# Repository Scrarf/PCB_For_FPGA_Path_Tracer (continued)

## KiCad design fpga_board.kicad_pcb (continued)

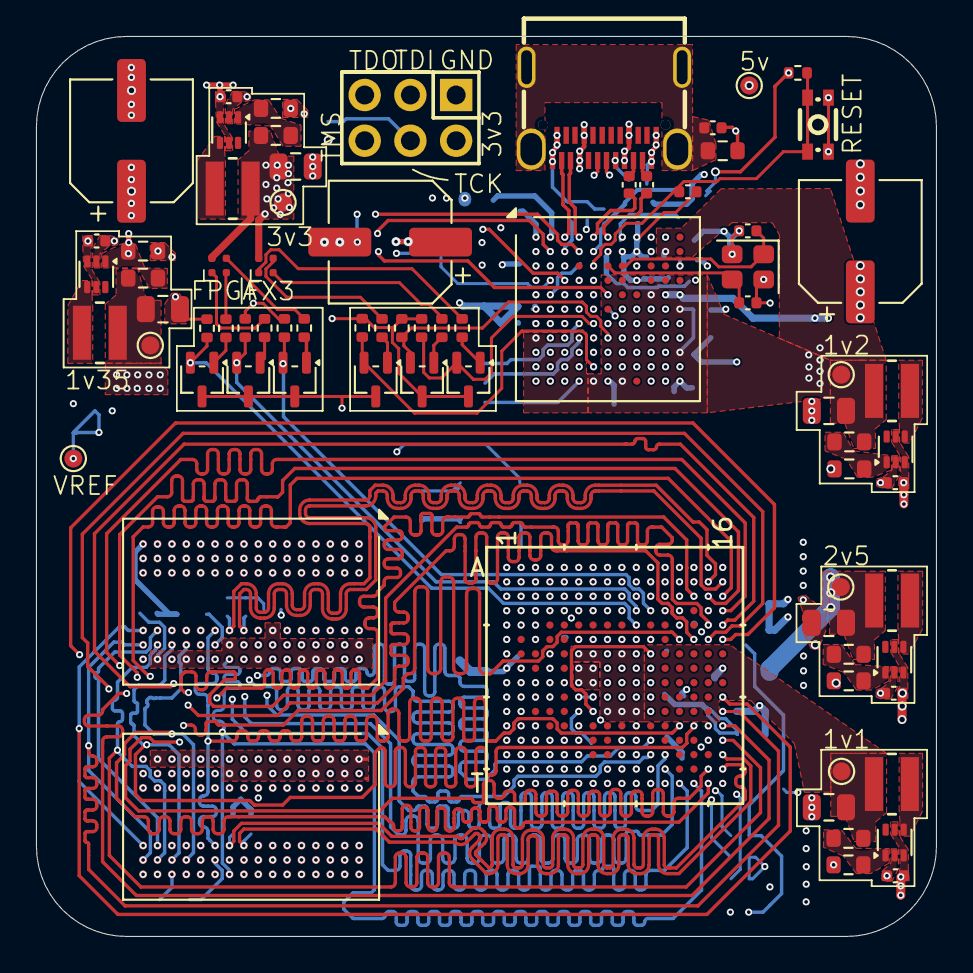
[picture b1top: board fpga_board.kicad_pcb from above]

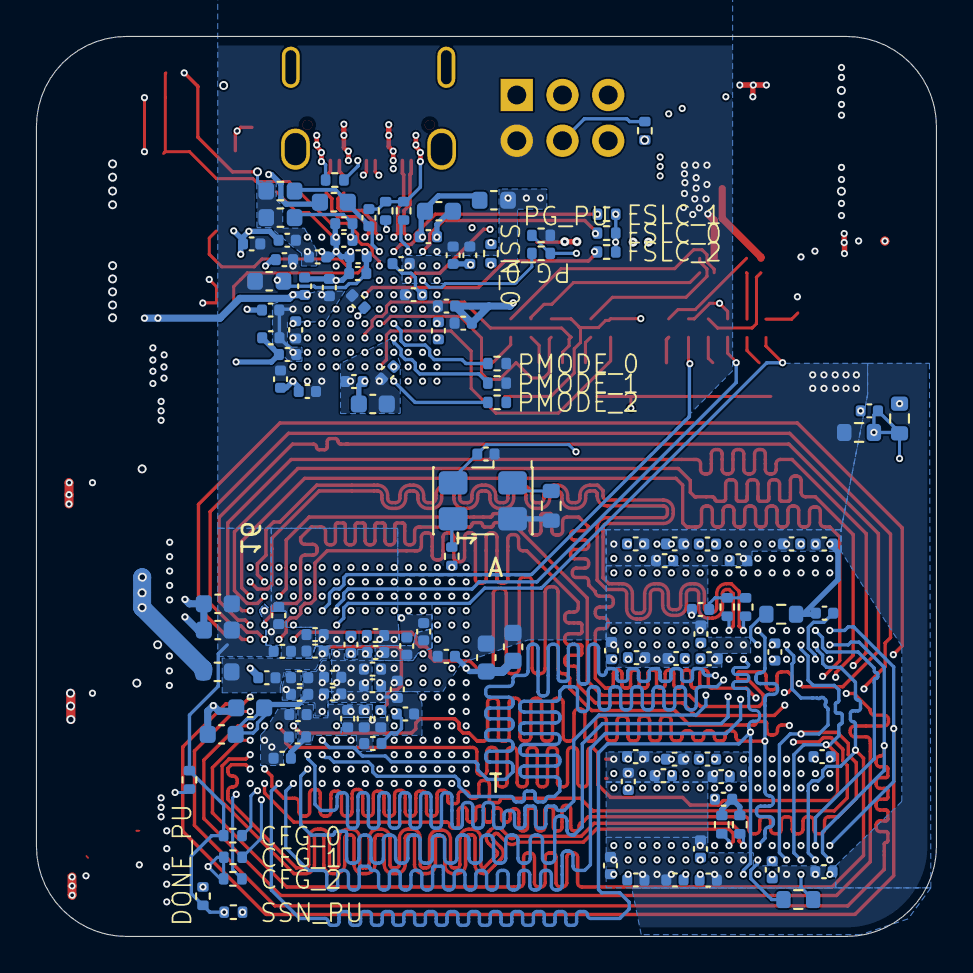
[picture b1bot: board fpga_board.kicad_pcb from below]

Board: 8 copper layers, 50.0 x 50.0 mm, 206 parts (130 on the bottom side), 201 nets.

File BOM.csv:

"Reference","Value","Datasheet","Qty","LCSC Part","Footprint","DNP","Tol"
"C1,C2,C3,C6,C10,C12,C13,C14,C16,C17,C20,C21,C24,C25,C38,C39,C40,C41,C42,C43,C44,C45,C46,C47,C48,C49,C50,C51,C52,C56,C57,C58,C59,C60,C62,C65,C67,C68,C69,C70,C71,C72,C77,C78,C79,C81,C83,C84,C85,C91,C92,C93,C94,C95,C96,C97,C98,C99,C100,C101,C102,C103,C104,C105,C106,C107,C108,C109,C110,C111,C112,C113","0.1µF","https://www.lcsc.com/datasheet/C60474.pdf","72","C60474","Capacitor_SMD:C_0402_1005Metric","",""
"C4,C5,C7,C53,C54,C55,C66,C80,C82","22µF","https://www.lcsc.com/datasheet/C6119868.pdf","9","C6119868","Capacitor_SMD:C_0603_1608Metric","",""
"C8,C9,C11,C18,C19,C22,C23,C26,C61,C89,C90","0.01µF","https://www.lcsc.com/datasheet/C22435944.pdf","11","C22435944","Capacitor_SMD:C_0402_1005Metric","",""
"C15,C29,C31,C33,C35,C37,C63","4.7µF","https://www.lcsc.com/datasheet/C6119786.pdf","7","C6119786","Capacitor_SMD:C_0402_1005Metric","",""
"C27,C28","15pF","https://www.lcsc.com/datasheet/C5448865.pdf","2","C5448865","Capacitor_SMD:C_0402_1005Metric","",""
"C30,C32,C34,C36,C64","47µF","https://www.lcsc.com/datasheet/C19103846.pdf","5","C19103846","Capacitor_SMD:C_0805_2012Metric","",""
"C73,C74,C75,C76,C86","10µF","https://www.lcsc.com/datasheet/C315248.pdf","5","C315248","Capacitor_SMD:C_0402_1005Metric","",""
"C87,C88,C114","100μF","https://www.lcsc.com/datasheet/C2887276.pdf","3","C2887276","Capacitor_SMD:CP_Elec_6.3x5.4","",""
"D1,D2","LED_RGBA","https://www.lcsc.com/datasheet/C22461780.pdf","2","C22461780","LED_SMD:LED_Wurth_150044M155260","",""
"FB1","120","https://www.lcsc.com/datasheet/C307770.pdf","1","C307770","Inductor_SMD:L_0603_1608Metric","",""
"H1","PH2.54-2X3P-H25","https://www.lcsc.com/datasheet/C42431837.pdf","1","C42431837","PIN-HEADER:HDR-TH_6P-P2.54-V-M-R2-C3-S2.54-1","",""
"L1,L2,L3,L4","BLM18KG601SN1D","https://www.lcsc.com/datasheet/C85833.pdf","4","C85833","Inductor_SMD:L_0603_1608Metric","",""
"L5,L6,L7,L8,L9","2.2µH","https://www.lcsc.com/datasheet/C42924311.pdf","5","C42924311","Inductor:IND_VLS3015_TDK","",""
"Q1,Q2,Q3,Q4,Q5,Q6","2N7002PW","https://www.lcsc.com/datasheet/C7379955.pdf","6","C7379955","Package_TO_SOT_SMD:SOT-323_SC-70","",""
"R1","6k04","https://www.lcsc.com/datasheet/C168240.pdf","1","C168240","Resistor_SMD:R_0402_1005Metric","","1%"
"R2","200","https://www.lcsc.com/datasheet/C25087.pdf","1","C49655161","Resistor_SMD:R_0402_1005Metric","","1%"
"R3,R4,R5,R6,R7,R8,R18,R19,R26,R27","0","https://www.lcsc.com/datasheet/C106231.pdf","10","C106231","Resistor_SMD:R_0402_1005Metric","",""
"R9,R10,R12,R14,R16,R38,R53","100k","https://www.lcsc.com/datasheet/C14675.pdf","7","C14675","Resistor_SMD:R_0603_1608Metric","","1%"
"R11","442k","https://www.lcsc.com/datasheet/C3013201.pdf","1","C3013201","Resistor_SMD:R_0603_1608Metric","","1%"
"R13","124k","https://www.lcsc.com/datasheet/C3016392.pdf","1","C3016392","Resistor_SMD:R_0603_1608Metric","","1%"
"R15","82k5","https://www.lcsc.com/datasheet/C2999460.pdf","1","C2999460","Resistor_SMD:R_0603_1608Metric","","1%"
"R17,R23,R25,R28,R29","4k7","https://www.lcsc.com/datasheet/C3017492.pdf","5","C3017492","Resistor_SMD:R_0402_1005Metric","",""
"R20,R21,R24","1k","https://www.lcsc.com/datasheet/C22548.pdf","3","C22548","Resistor_SMD:R_0603_1608Metric","","1%"
"R22,R37","240","https://www.lcsc.com/datasheet/C49653074.pdf","2","C49653074","Resistor_SMD:R_0603_1608Metric","","1%"
"R30,R31,R33,R35,R41,R42,R43","10k","https://www.lcsc.com/datasheet/C51035904.pdf","7","C51035904","Resistor_SMD:R_0402_1005Metric","",""
"R32,R34,R45,R46,R47","20","https://www.lcsc.com/datasheet/C3017453.pdf","5","C3017453","Resistor_SMD:R_0402_1005Metric","",""
"R36,R44","62","https://www.lcsc.com/datasheet/C49653021.pdf","2","C49653021","Resistor_SMD:R_0402_1005Metric","",""
"R39","5k1","https://www.lcsc.com/datasheet/C49652827.pdf","1","C49652827","Resistor_SMD:R_0402_1005Metric","",""
"R40","330","https://www.lcsc.com/datasheet/C2906929.pdf","1","C2906929","Resistor_SMD:R_0402_1005Metric","",""
"R48,R49,R50,R51","50","https://www.lcsc.com/datasheet/C853312.pdf","4","C853312","Resistor_SMD:R_0402_1005Metric","","1%"
"R52","319k","https://www.lcsc.com/datasheet/C20165692.pdf","1","C20165692","Resistor_SMD:R_0603_1608Metric","","1%"
"SW1","1TS028A-1300-0600-CT","https://www.lcsc.com/datasheet/C481983.pdf","1","C481983","BUTTON:SW-SMD_4P-L2.8-W1.9-P1.20-LS3.0_1TS028A","",""
"U1","LFE5U-45F-6BG256C","https://www.lcsc.com/datasheet/C1550826.pdf","1","C1550834","ECP5:caBGA256_LAT","",""
"U2","CYUSB3014-BZXC","https://www.lcsc.com/datasheet/C462526.pdf","1","C462526","Package_BGA:TFBGA-121_10x10mm_Layout11x11_P0.8mm","",""
"U3,U7,U8,U9,U10","TLV62569DRL","https://www.lcsc.com/datasheet/C163217.pdf","5","C163217","Package_TO_SOT_SMD:SOT-563","",""
"U5,U6","MT41K256M16TW-093:P","https://www.lcsc.com/datasheet/C2064402.pdf","2","C2064402","Package_BGA:Micron_FBGA-96_9x14mm_Layout9x16_P0.8mm","",""
"USB1","TYPE-C 24P QT 143","https://www.lcsc.com/datasheet/C5156605.pdf","1","C5156605","USB-TYPE-C:TYPE-C-SMD_C9900025773","",""
"X1","XO32","https://www.lcsc.com/datasheet/C50345411.pdf","1","C50345411","Crystal:Crystal_SMD_5032-4Pin_5.0x3.2mm","",""
"Y1","Crystal_GND24","https://www.lcsc.com/datasheet/C7206296.pdf","1","C7206296","Crystal:Crystal_SMD_2520-4Pin_2.5x2.0mm","",""

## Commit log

2025-10-17 Inception
2025-10-17 added lib
2025-10-17 added readme
2025-10-25 changed FPGA to 45k cuz old one went out of stock :(
2025-10-25 DQ lane busses are assigned to apropriate DQS lanes and ready
2025-10-25 DQ and DQS group busses complete
2025-10-27 removed DQS groups instead added DDR3 pin busses
2025-10-27 added colors and bunch of other stuff idk
2025-10-30 ddr wiring and other stuff
2025-11-01 layer 3 FX3 length matched
2025-11-02 minor changes
2025-11-08 changed stackup
2025-11-21 added FPGA oscillator
2025-11-22 added SPI connections and FX3 RGB LED. Decided to go with 2 dram chips instead for 4 for 32bit bus
2025-12-06 added spi pins and FX3 crystal capacitors and allat and idk other stuff
2025-12-06 added capacitor and resistor footprints
2025-12-09 added RGB LED for FPGA, added termintaion to FPGA crystal
2025-12-11 update to kicad 9.0.6 and other changes
2025-12-13 added LCSC footprint libraries
2025-12-13 finished schematic, finished BOM.
2025-12-13 added pre-commit for schematic svg generation, edited readme, organized schematic.
2025-12-13 added layout svg to readme
2025-12-13 fixed readme error and other cosmetic fixes
2025-12-13 another minor readme change
2025-12-15 layout: buck converters placed
2025-12-18 BYTE_LANE 0 and 1 routed and length matched to DDR memory
2025-12-20 all DDR byte lanes routed and length matched
2025-12-23 trying to set up EM simulation for DDR DQ lanes
2025-12-27 moved EM simulation part to a different repo
2025-12-28 fill zone clearences decreased and .glb exported again
2026-01-21 .glb file export to blender
2026-01-30 migration from windows to linux, also ACC pins partially finished
2026-01-30 removed unnesessary html import guides
2026-01-30 organized ACC clock DDR. not fully routed yet
2026-02-02 ACC F.Cu routed and length matched
2026-02-02 ACC pins completed.
2026-02-03 added 2v5 buck converter
2026-02-07 FIFO_DQ and FIFO_CTRL lanes routed and length matched
2026-02-08 USB 2.0 and USB 3.0 routed. UBS 3.0 Differential pair polarity reversed
2026-02-12 wired DRAM_VREF including divider and decaps, also wired SPI program pins from FX3 to FPGA
2026-02-12 fpga active oscillator pin changed and layout fully constructed. B.Cu ACC lines slightly modified and FPGA fifo lanes slightly modified to free GPLL input pin
2026-02-12 oscillator core voltage fixed. changed from 1v35 to 3v3.
2026-02-12 2v5 and 1v1 wired but needs power integrity tests
2026-02-15 added FX3 RGB in layout. wired 1v2 FX3 core. wired DONE pullup.
2026-02-15 updated DDR3 footprint BGA diameter from 0.4mm to 0.45mm for better stability I guess?
2026-02-15 updated FX3 footprint to remove warning
2026-02-19 ZQ resistors added to layout
2026-02-21 added correct decoupling in schematic for FPGA, currently working on layout.
2026-02-23 FPGA decoupling capacitors finished
2026-02-23 organizing configuration resistors on layout
2026-02-24 cleared footprint booard and library missmatch warnings
2026-02-25 rearanged RGB LEDs, added 3D models for most components, Added Electrolytic capacitors for VBUS, changed position of JTAG pins and other minor details
2026-02-25 removed unused silkscreens
2026-02-26 added kiri to .gitignore. changed FX3 configuration resistor position.
2026-02-26 added FX3 decaps (no power yet).
2026-02-28 FX decoupling and power finished
2026-02-28 fixed ACC length matching on B.Cu and F.Cu.
2026-03-01 DDR3 decoupling finished.
2026-03-02 cosmetic siklscreen changes and moved some footprints for better silkscreen availability. Added another 0 ohm resistor for PMODE (PMODE_2). Labeled configuration resistors.
2026-03-02 Added Another 100μF capacitor because I have empty space why not plus it looks cooler
2026-03-03 fixed some errors with JLCDFM
2026-03-03 changed some component values to reduce BOM cost, updated sheets for out of stock components.
2026-03-03 Switched VREF testpoint to F.Cu and removed Testpoints from BOM
2026-03-03 moved layout to page center for no reason
2026-03-05 added propper BOM.csv, added NC signs on unconnected pins.
2026-03-05 included gerber in from .gitignore
2026-03-07 changed buck converter output capacitors from 10 to 47 microfarad.
2026-03-07 updated gerber files
2026-03-11 BOM.csv updated 200ohm resistor went out of stock
2026-03-17 Final commit before production
